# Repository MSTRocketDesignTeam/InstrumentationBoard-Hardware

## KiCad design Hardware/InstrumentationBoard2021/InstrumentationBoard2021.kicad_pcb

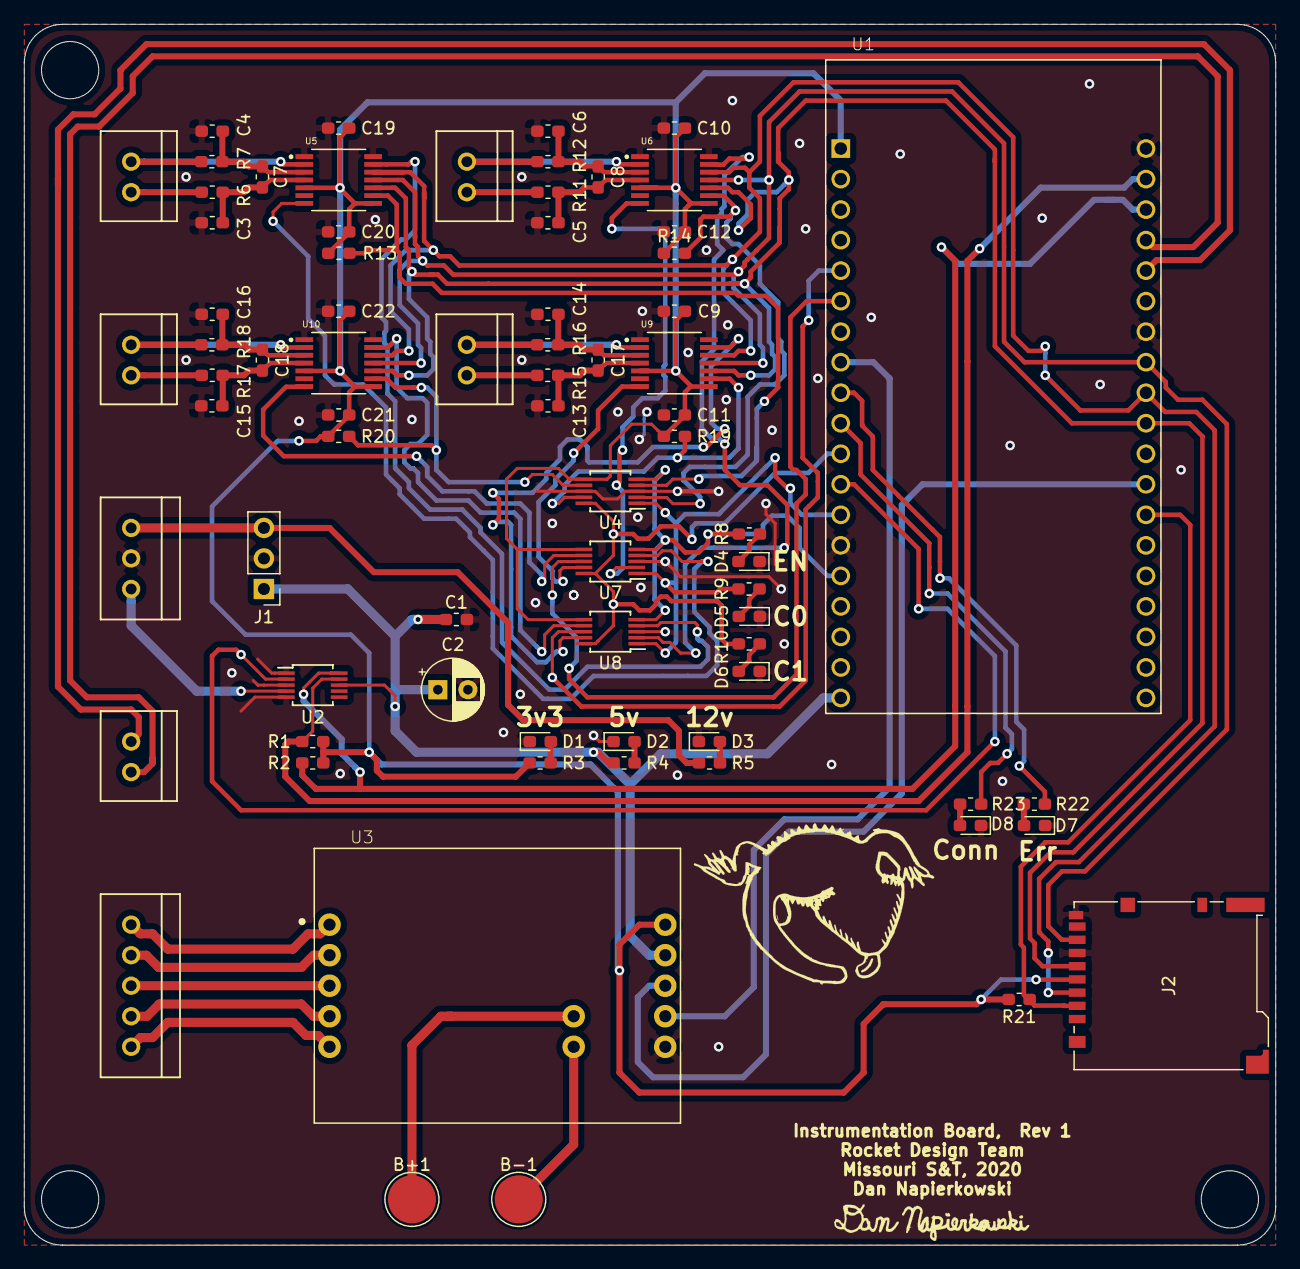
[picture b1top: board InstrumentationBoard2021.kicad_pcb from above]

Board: 2 copper layers, 104.1 x 101.6 mm, 74 parts (0 on the bottom side), 66 nets.

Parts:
B+1: TestPoint; TestPoint_Pad_D4.0mm
B-1: TestPoint; TestPoint_Pad_D4.0mm
C1: .1uF; C_0603_1608Metric_Pad1.05x0.95mm_HandSolder
C2: 33uF; CP_Radial_D5.0mm_P2.50mm
C3, C4, C5, C6, C13, C14, C15, C16: 0.01uF; C_0603_1608Metric_Pad1.05x0.95mm_HandSolder
C7, C8, C9, C10, C11, C12, C17, C18, C19, C20, C21, C22: 0.1uF; C_0603_1608Metric_Pad1.05x0.95mm_HandSolder
Conn1: Molex_SL_05; MOLEX_SL_05_Vertical
Conn2: Molex_SL_03; MOLEX_SL_03_Vertical
Conn3, Conn4, Conn5, Conn6, Conn7: Molex_SL_02; MOLEX_SL_02_Vertical
D1, D2, D3, D4, D5, D6, D7, D8: LED; LED_0603_1608Metric_Pad1.05x0.95mm_HandSolder
J1: Conn_01x03_Male; PinHeader_1x03_P2.54mm_Vertical
J2: Micro_SD_Card; microSD_HC_Hirose_DM3BT-DSF-PEJS
R1, R2, R13, R14, R19, R20, R21: 10k; R_0603_1608Metric_Pad1.05x0.95mm_HandSolder
R3, R8, R9, R10, R22, R23: 330; R_0603_1608Metric_Pad1.05x0.95mm_HandSolder
R4: 500; R_0603_1608Metric_Pad1.05x0.95mm_HandSolder
R5: 1k; R_0603_1608Metric_Pad1.05x0.95mm_HandSolder
R6, R7, R11, R12, R15, R16, R17, R18: 100; R_0603_1608Metric_Pad1.05x0.95mm_HandSolder
U1: ESP32-DEVKITC-32D; MODULE_ESP32-DEVKITC-32D
U2: ADS1114; MSOP-10_3x3mm_P0.5mm
U3: SEN-13879; SPARKFUN_SEN-13879
U4, U7, U8: TMUX1104; MSOP-10_3x3mm_P0.5mm
U5, U6, U9, U10: MAX31856MUD+; SOP65P640X110-14N

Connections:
+3V3: C9.1, C10.1, C11.1, C12.1, C19.1, C20.1, C21.1, C22.1, J2.4, R1.1, R2.1, R3.2, R13.1, R14.1, R19.1, R20.1, R21.2, U1.1, U3.10, U4.6, U5.5, U5.8, U6.5, U6.8, U7.6, U8.6, U9.5, U9.8, U10.5, U10.8
+5V: C1.1, C2.1, J1.1, R4.2, U1.19, U2.8, U3.9
+12V: Conn2.1, J1.3, R5.2
/ESP32/LC_DOUT: U1.31, U3.8
/ESP32/LC_SCK: U1.8, U3.7
/ESP32/LoadCell_RX: Conn3.1, U1.24
/ESP32/LoadCell_TX: Conn3.2, U1.23
/ESP32/MISO: J2.7, U1.27, U5.11, U6.11, U9.11, U10.11
/ESP32/MOSI: J2.3, U1.28, U5.12, U6.12, U9.12, U10.12
/ESP32/PT_RDY: U1.12, U2.2
/ESP32/PT_SCL: R2.2, U1.22, U2.10
/ESP32/PT_SDA: R1.2, U1.21, U2.9
/ESP32/SCK: J2.5, U1.29, U5.10, U6.10, U9.10, U10.10
/ESP32/SDCard_CS: J2.2, R21.1, U1.32
/ESP32/TC_C0: R9.1, U1.13, U4.1, U7.1, U8.1
/ESP32/TC_C1: R10.1, U1.11, U4.10, U7.10, U8.10
/ESP32/TC_DRDY: U1.6, U7.8
/ESP32/TC_EN: R8.1, U1.15, U4.5, U7.5, U8.5
/ESP32/TC_FAULT: U1.5, U8.8
/ThermoCouples/Tm_1: Conn4.1, R12.1, U6.2
/ThermoCouples/Tm_2: Conn5.1, R16.1, U9.2
/ThermoCouples/Tm_3: Conn6.1, R7.1, U5.2
/ThermoCouples/Tm_4: Conn7.1, R18.1, U10.2
/ThermoCouples/Tp_1: Conn4.2, R11.1
/ThermoCouples/Tp_2: Conn5.2, R15.1
/ThermoCouples/Tp_3: Conn6.2, R6.1
/ThermoCouples/Tp_4: Conn7.2, R17.1
CS_1: R14.2, U4.2, U6.9
CS_2: R19.2, U4.9, U9.9
CS_3: R13.2, U4.4, U5.9
CS_4: R20.2, U4.7, U10.9
DRDY_1: U6.7, U7.2
DRDY_2: U7.9, U9.7
DRDY_3: U5.7, U7.4
DRDY_4: U7.7, U10.7
FAULT_1: U6.13, U8.2
FAULT_2: U8.9, U9.13
FAULT_3: U5.13, U8.4
FAULT_4: U8.7, U10.13
GND: C1.2, C2.2, C3.1, C4.1, C5.1, C6.1, C9.2, C10.2, C11.2, C12.2, C13.1, C14.1, C15.1, C16.1, C19.2, C20.2, C21.2, C22.2, Conn2.2, D1.1, D2.1, D3.1, D4.1, D5.1, D6.1, D7.1, D8.1, J1.2, J2.6, J2.9, U1.14, U1.20, U1.26, U2.1, U2.3, U2.5, U3.6, U4.3, U4.8, U5.1, U5.14, U6.1, U6.14, U7.3, U8.3, U9.1, U9.14, U10.1, U10.14
unnamed: B+1.1, U3.11
unnamed: B-1.1, U3.12
unnamed: C3.2, C7.1, R6.2, U5.4
unnamed: C4.2, C7.2, R7.2, U5.3
unnamed: C5.2, C8.1, R11.2, U6.4
unnamed: C6.2, C8.2, R12.2, U6.3
unnamed: C13.2, C17.1, R15.2, U9.4
unnamed: C14.2, C17.2, R16.2, U9.3
unnamed: C15.2, C18.1, R17.2, U10.4
unnamed: C16.2, C18.2, R18.2, U10.3
unnamed: Conn1.1, U3.1
unnamed: Conn1.2, U3.2
unnamed: Conn1.3, U3.3
unnamed: Conn1.4, U3.4
unnamed: Conn1.5, U3.5
unnamed: Conn2.3, U2.4
unnamed: D1.2, R3.1
unnamed: D2.2, R4.1
unnamed: D3.2, R5.1
unnamed: D4.2, R8.2
unnamed: D5.2, R9.2
unnamed: D6.2, R10.2
unnamed: D7.2, R22.2
unnamed: D8.2, R23.2
unnamed: R22.1, U1.9
unnamed: R23.1, U1.10

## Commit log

2020-12-10 made board
2021-04-14 asfhlakjsh
